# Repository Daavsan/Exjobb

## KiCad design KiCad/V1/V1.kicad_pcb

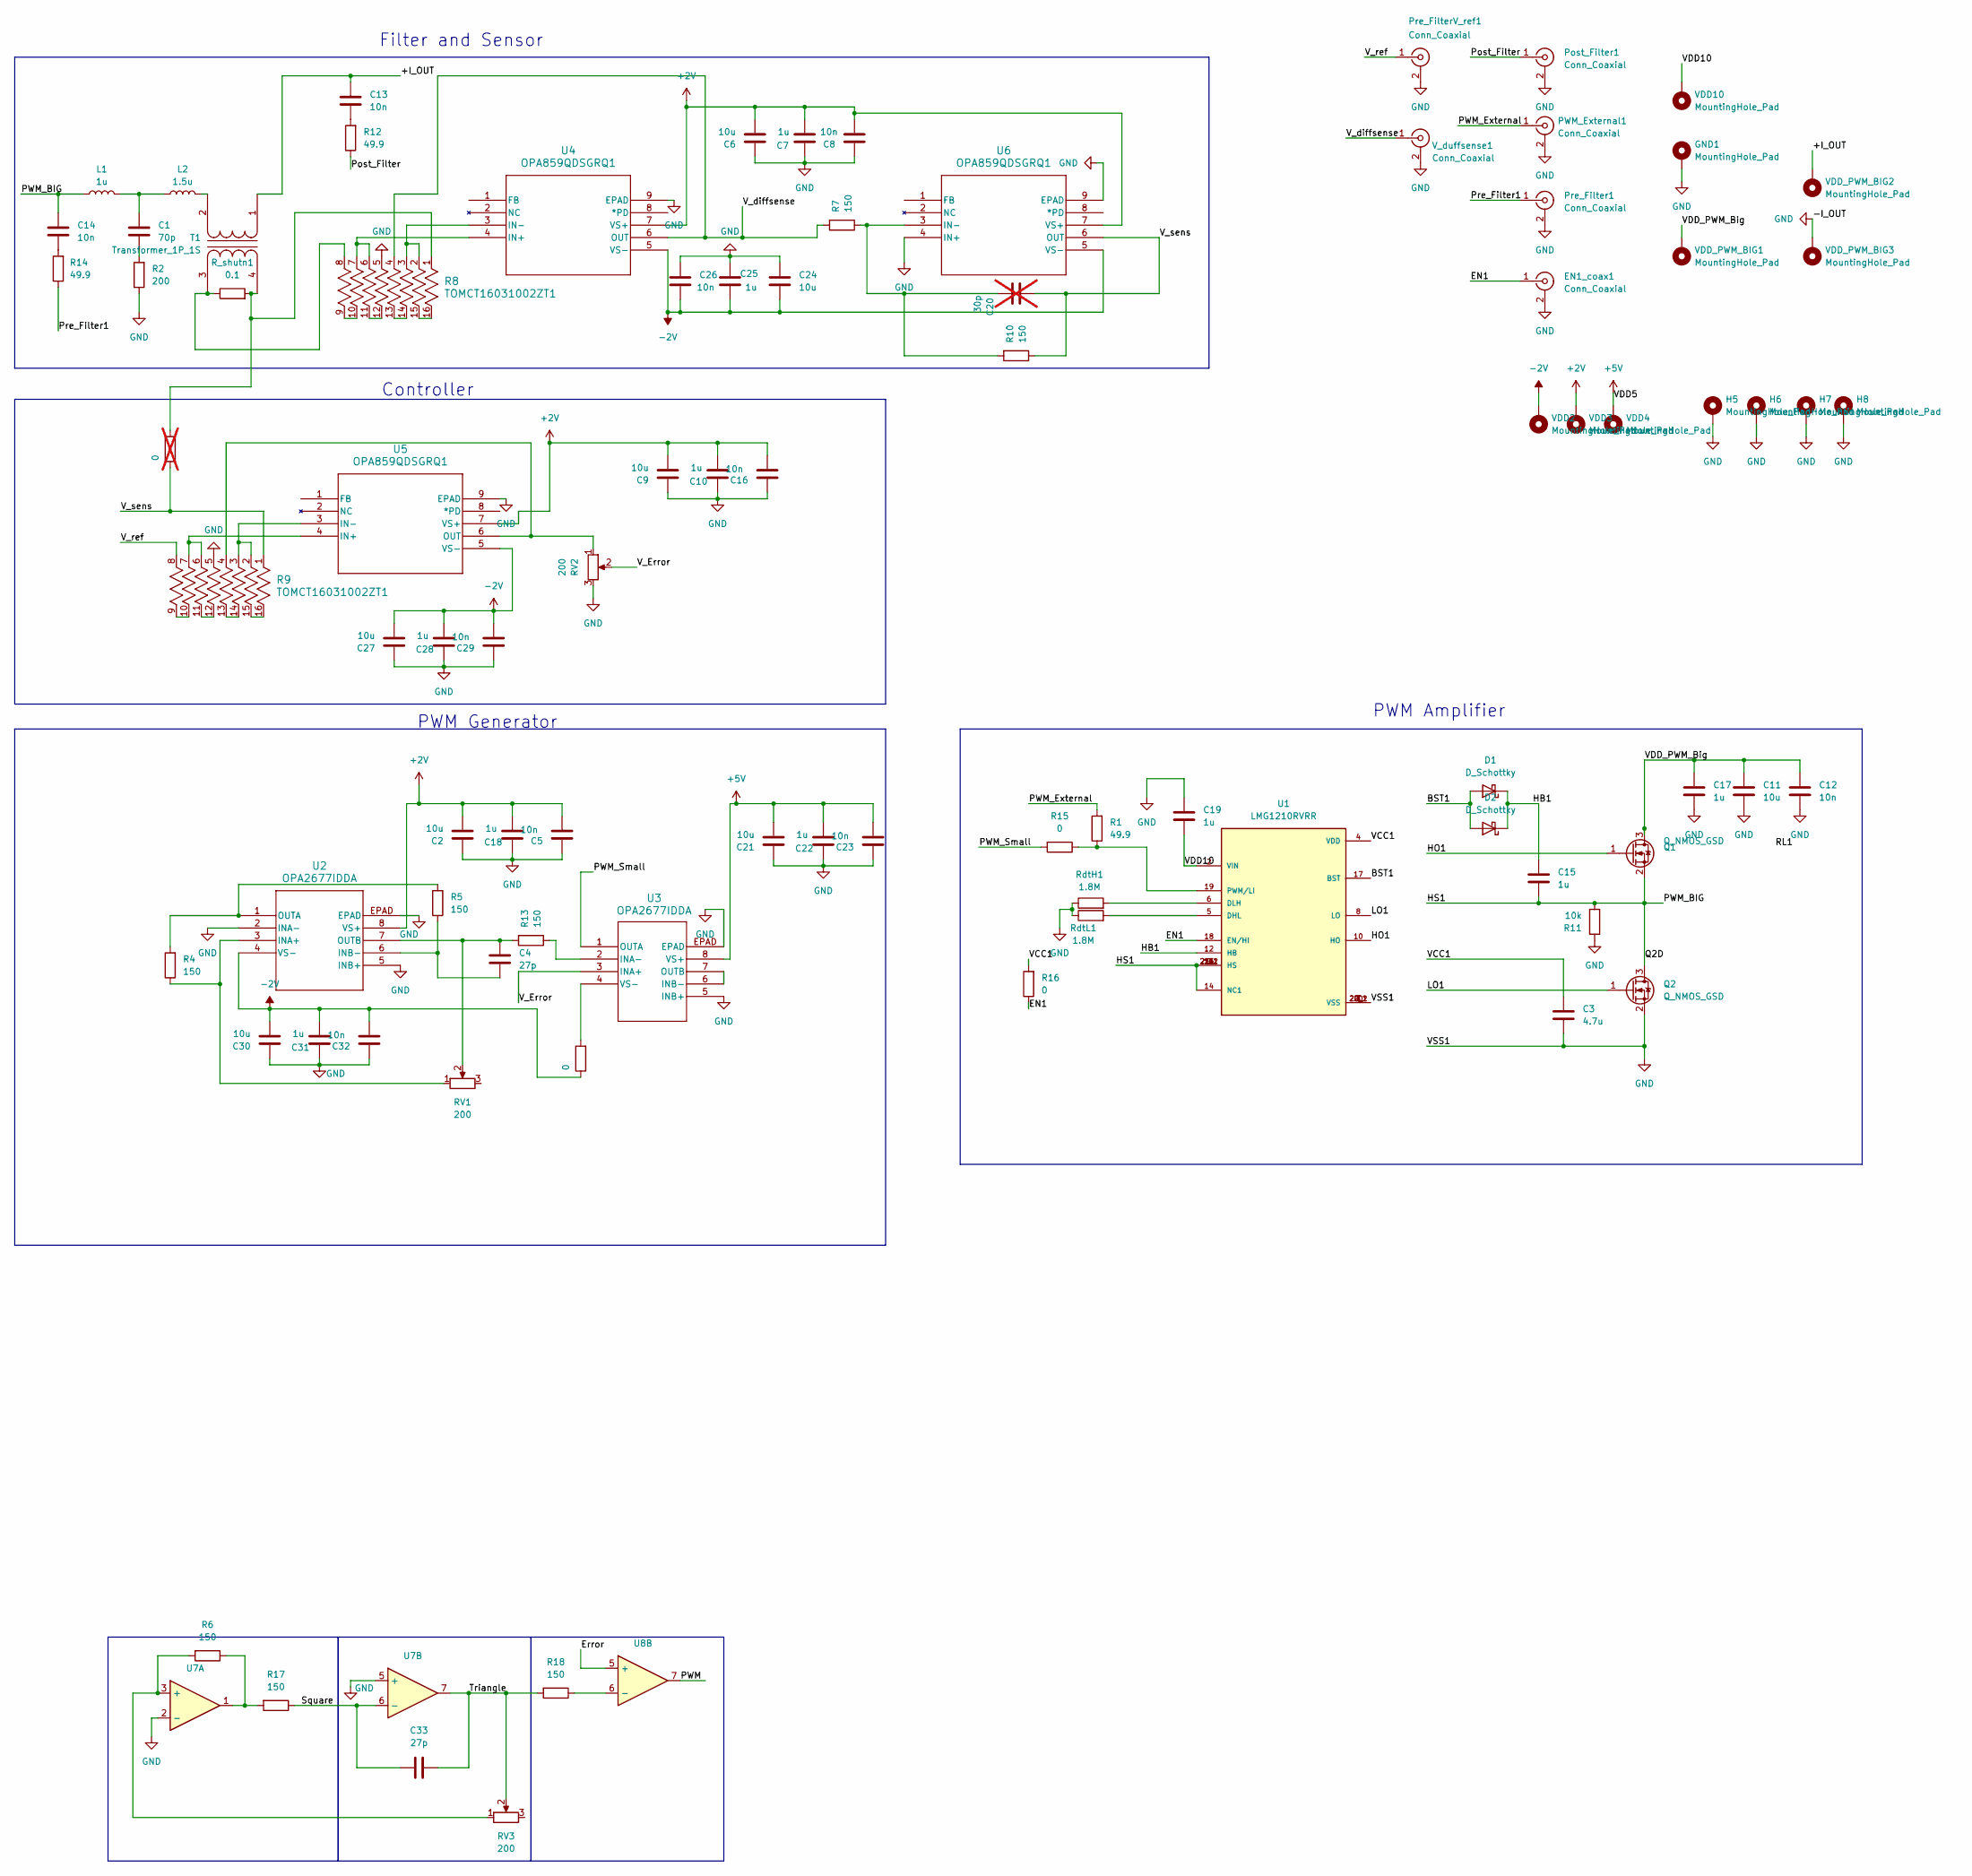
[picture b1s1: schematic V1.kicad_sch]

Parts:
C1: 70p; R_1206_3216Metric
C2, C21, C30: 10u; C_0402_1005Metric
C3: 4.7u; C_0603_1608Metric
C4, C33: 27p; C_0402_1005Metric
C5, C8, C13, C14, C16, C23, C26, C29, C32: 10n; C_0402_1005Metric
C6, C9, C24, C27: 10u; C_0603_1608Metric
C7, C10, C15, C18, C19, C22, C25, C28, C31: 1u; C_0402_1005Metric
C11: 10u; C_2220_5750Metric
C12: 10n; C_0805_2012Metric
C17: 1u; C_0805_2012Metric
C20: 30p; C_0402_1005Metric; not fitted
D1, D2: D_Schottky; SOT-323_SC-70
EN1_coax1: Conn_Coaxial; U.FL_Molex_MCRF_73412-0110_Vertical
GND1: MountingHole_Pad; MountingHole_2.5mm_Pad_TopBottom
H5, H6, H7, H8: MountingHole_Pad; MountingHole_4.3mm_M4_DIN965_Pad_TopBottom
L1: 1u; INductor_744060421
L2: 1.5u; INductor_744060421
PWM_External1: Conn_Coaxial; U.FL_Molex_MCRF_73412-0110_Vertical
Post_Filter1: Conn_Coaxial; U.FL_Molex_MCRF_73412-0110_Vertical
Pre_Filter1: Conn_Coaxial; U.FL_Molex_MCRF_73412-0110_Vertical
Pre_FilterV_ref1: Conn_Coaxial; U.FL_Molex_MCRF_73412-0110_Vertical
Q1, Q2: Q_NMOS_GSD; EPC8009
R1, R12, R14: 49.9; R_0402_1005Metric
R2: 200; R_1206_3216Metric
R3, R15, R16: 0; C_0805_2012Metric
R4, R5, R7, R10, R13: 150; R_0402_1005Metric
R6, R17, R18: 150
R8, R9: TOMCT16031002ZT1; NOMCT16031
R11: 10k; R_0402_1005Metric
R19: 0; C_0805_2012Metric; not fitted
RV1, RV2, RV3: 200; POT_ 3214W-1-201E
R_shutn1: 0.1; R_1020_2550Metric_Pad1.33x5.20mm_HandSolder
RdtH1: 1.8M; R_0402_1005Metric
RdtL1: 1.8M; R_0402_1005Metric
T1: Transformer_1P_1S; MyTransformer
U1: LMG1210RVRR; IC_LMG1210RVRR; PARTREV D
U2, U3: OPA2677IDDA; DDA8_3X2P49
U4, U5, U6: OPA859QDSGRQ1
U7: OPAMP
U8: Compariotr
VDD2, VDD3, VDD4, VDD10: MountingHole_Pad; TestPoint_THTPad_D2.5mm_Drill1.2mm
VDD_PWM_BIG1, VDD_PWM_BIG2, VDD_PWM_BIG3: MountingHole_Pad; MountingHole_2.5mm_Pad_TopBottom
V_duffsense1: Conn_Coaxial; U.FL_Molex_MCRF_73412-0110_Vertical

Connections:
+2V: C2.2, C5.2, C6.2, C7.2, C8.2, C9.2, C10.2, C16.2, C18.2, U2.8 (VS+), U4.7 (VS+), U5.7 (VS+), U6.7 (VS+), VDD3.1
+5V: C21.2, C22.2, C23.2, U3.8 (VS+), VDD4.1
-2V: C24.2, C25.2, C26.2, C27.2, C28.2, C29.2, C30.2, C31.2, C32.2, R3.1, U2.4 (VS-), U4.5 (VS-), U5.5 (VS-), U6.5 (VS-), VDD2.1
/+I_OUT: C13.2, T1.1 (AA), VDD_PWM_BIG2.1
/BST1: D1.1 (A), D2.1 (A), U1.17 (BST)
/EN1: EN1_coax1.1 (In), R16.1, U1.18 (EN/HI)
/HB1: C15.1, D1.3 (K), D2.3 (K), U1.12 (HB)
/HO1: Q1.1 (G), U1.10 (HO)
/HS1: C14.2, C15.2, L1.1, Q1.2 (S), Q2.3 (D), R11.1, U1.9 (HS), U1.13 (HS), U1.14 (NC1), U1.16 (HS), U1.21 (HS), U1.21_1 (HS), U1.21_2 (HS)
/LO1: Q2.1 (G), U1.8 (LO)
/PWM_External: PWM_External1.1 (In), R1.2
/PWM_Small: R15.2, U3.1 (OUTA)
/Post_Filter: Post_Filter1.1 (In), R12.1
/Pre_Filter1: Pre_Filter1.1 (In), R14.1
/VCC1: C3.1, R16.2, U1.4 (VDD)
/VDD10: C19.2, U1.2 (VIN), VDD10.1
/VDD_PWM_Big: C11.1, C12.1, C17.1, Q1.3 (D), VDD_PWM_BIG1.1
/V_Error: RV2.2, U3.3 (INA+)
/V_diffsense: R7.2, R8.4, U4.6 (OUT), V_duffsense1.1 (In)
/V_ref: Pre_FilterV_ref1.1 (In), R9.8
/V_sens: C20.1, R9.1, R10.1, R19.1, U6.6 (OUT)
GND: C2.1, C3.2, C5.1, C6.1, C7.1, C8.1, C9.1, C10.1, C11.2, C12.2, C16.1, C17.2, C18.1, C19.1, C21.1, C22.1, C23.1, C24.1, C25.1, C26.1, C27.1, C28.1, C29.1, C30.1, C31.1, C32.1, EN1_coax1.2 (Ext), GND1.1, H5.1, H6.1, H7.1, H8.1, PWM_External1.2 (Ext), Post_Filter1.2 (Ext), Pre_Filter1.2 (Ext), Pre_FilterV_ref1.2 (Ext), Q2.2 (S), R2.1, R8.5, R9.5, R11.2, RV2.3, RdtH1.1, RdtL1.1, U1.3 (VSS), U1.7 (VSS), U1.20 (VSS), U1.20_1 (VSS), U1.20_2 (VSS), U2.2 (INA-), U2.5 (INB+), U2.EPAD, U3.5 (INB+), U3.EPAD, U4.9 (EPAD), U5.9 (EPAD), U6.4 (IN+), U6.9 (EPAD), U7.2 (-), U7.5 (+), VDD_PWM_BIG3.1, V_duffsense1.2 (Ext)
unnamed: C1.1, L1.2, L2.1
unnamed: C1.2, R2.2
unnamed: C13.1, R12.2
unnamed: C14.1, R14.2
unnamed: C33.1, R17.1, U7.6 (-)
unnamed: C33.2, R18.2, RV3.2, U7.7
unnamed: R6.2, RV3.1, U7.3 (+)
unnamed: R8.9, R8.10
unnamed: R8.11, R8.12
unnamed: R8.13, R8.14
unnamed: R8.15, R8.16
unnamed: R9.9, R9.10
unnamed: R9.11, R9.12
unnamed: R9.13, R9.14
unnamed: R9.15, R9.16
unnamed: R6.1, R17.2, U7.1
unnamed: R18.1, U8.6 (-)
unnamed: L2.2, T1.2 (AB)
unnamed: R8.8, R_shutn1.1, T1.3 (SA)
unnamed: R8.1, R19.2, R_shutn1.2, T1.4 (SB)
unnamed: RdtL1.2, U1.5 (DHL)
unnamed: RdtH1.2, U1.6 (DLH)
unnamed: R1.1, R15.1, U1.19 (PWM/LI)
unnamed: R4.1, RV1.1, U2.3 (INA+)
unnamed: C4.1, R5.1, U2.6 (INB-)
unnamed: R4.2, R5.2, U2.1 (OUTA)
unnamed: C4.2, R13.2, RV1.2, U2.7 (OUTB)
unnamed: R13.1, U3.2 (INA-)
unnamed: U3.6 (INB-), U3.7 (OUTB)
unnamed: R3.2, U3.4 (VS-)
unnamed: R8.6, R8.7, U4.4 (IN+)
unnamed: R8.2, R8.3, U4.3 (IN-)
unnamed: R9.6, R9.7, U5.4 (IN+)
unnamed: R9.2, R9.3, U5.3 (IN-)
unnamed: R9.4, RV2.1, U5.6 (OUT)
unnamed: C20.2, R7.1, R10.2, U6.3 (IN-)

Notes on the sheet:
Controller
Filter and Sensor
PWM Generator
PWM Amplifier

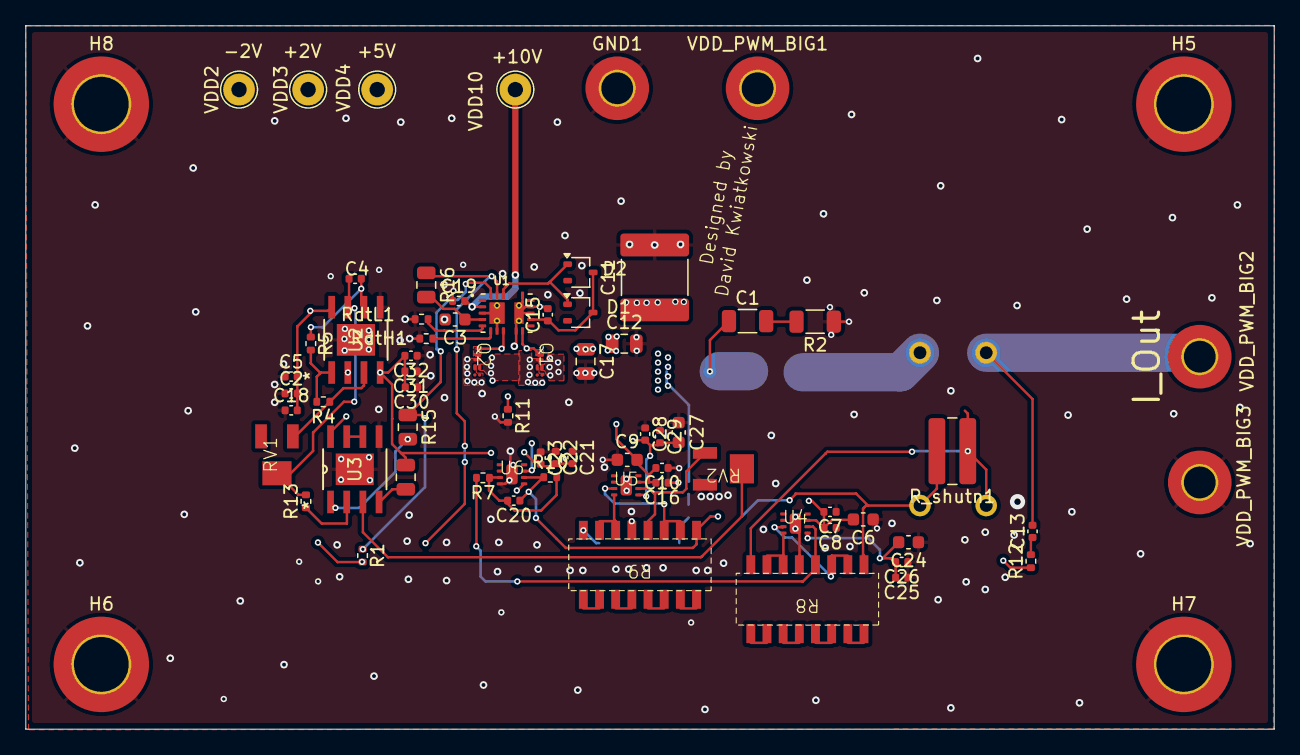
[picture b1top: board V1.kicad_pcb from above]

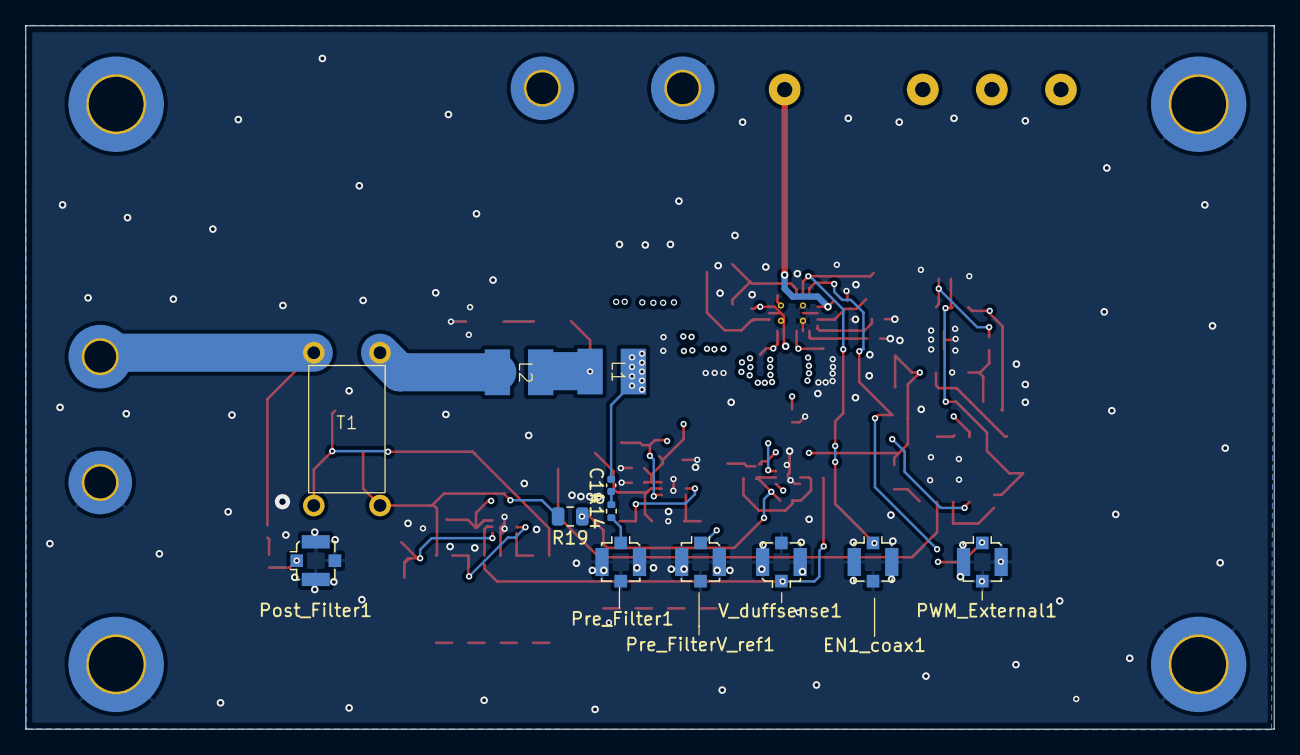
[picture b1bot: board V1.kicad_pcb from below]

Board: 4 copper layers, 98.0 x 55.2 mm, 84 parts (12 on the bottom side), 53 nets.

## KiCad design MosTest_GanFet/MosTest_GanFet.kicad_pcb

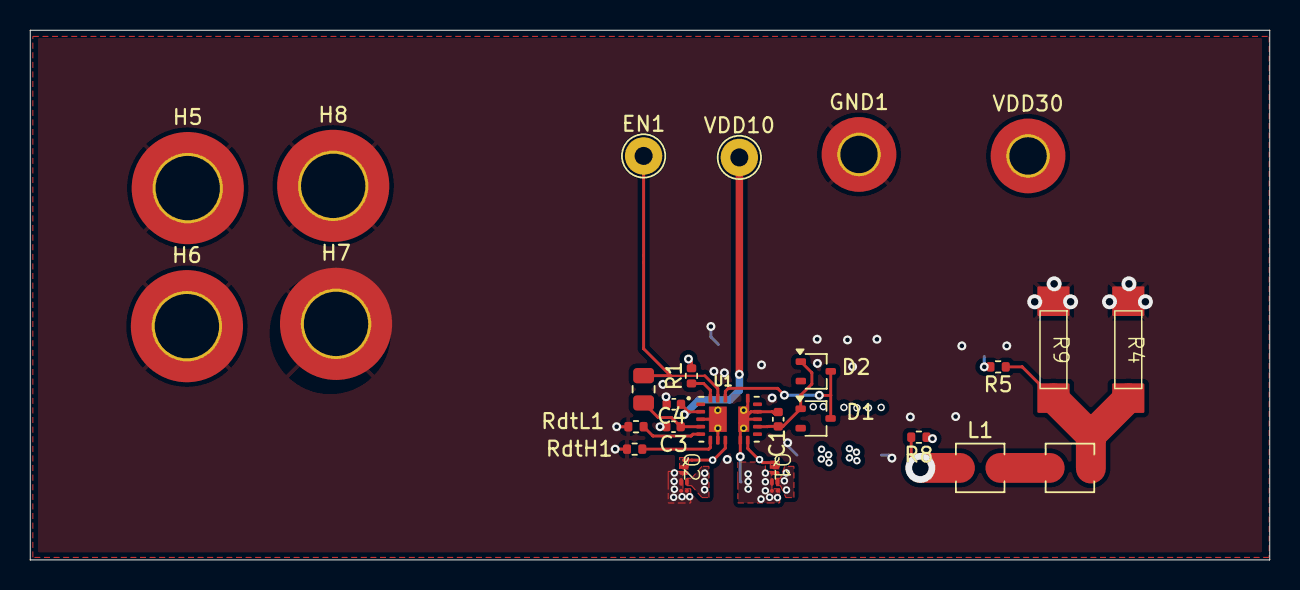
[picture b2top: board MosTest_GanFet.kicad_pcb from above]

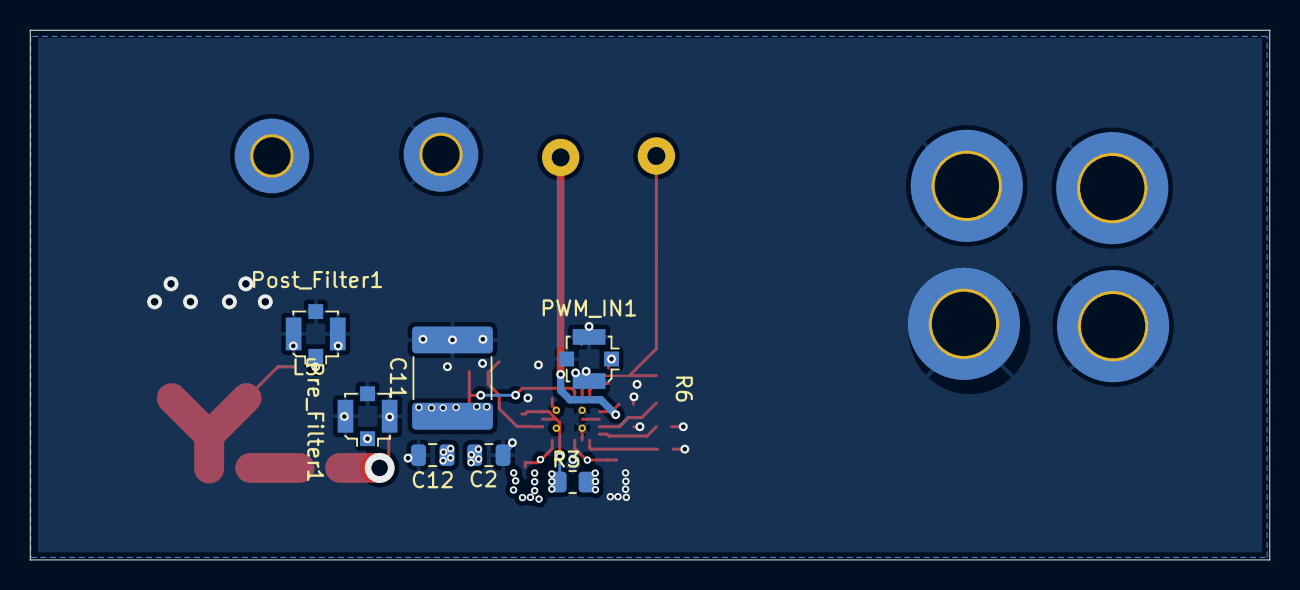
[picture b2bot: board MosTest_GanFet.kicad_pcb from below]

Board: 4 copper layers, 82.9 x 35.4 mm, 33 parts (7 on the bottom side), 19 nets.

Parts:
C1, C4: 1u; C_0402_1005Metric
C2: 1u; C_0805_2012Metric
C3: 4.7u; C_0402_1005Metric
C11: 22u; C_2220_5750Metric
C12: 10n; C_0805_2012Metric
D1, D2: D_Schottky; SOT-323_SC-70
EN1: MountingHole_Pad; TestPoint_THTPad_D2.5mm_Drill1.2mm
GND1: MountingHole_Pad; MountingHole_2.5mm_Pad_TopBottom
H5, H6, H7, H8: MountingHole_Pad; MountingHole_4.3mm_M4_DIN965_Pad_TopBottom
L1, L5: L; L_Vishay_IHLP-1212
PWM_IN1: Conn_Coaxial; U.FL_Molex_MCRF_73412-0110_Vertical
Post_Filter1: Conn_Coaxial; U.FL_Molex_MCRF_73412-0110_Vertical
Pre_Filter1: Conn_Coaxial; U.FL_Molex_MCRF_73412-0110_Vertical
Q1, Q2: Q_NMOS_GSD; EPC8009
R1, R5, R8: 47; R_0402_1005Metric
R3, R6: 0; R_0805_2012Metric
R4, R9: 470; RWS5
RdtH1: 1.8M; R_0402_1005Metric
RdtL1: 1.8M; R_0402_1005Metric
U1: LMG1210RVRR; IC_LMG1210RVRR
VDD10: MountingHole_Pad; TestPoint_THTPad_D2.5mm_Drill1.2mm
VDD30: MountingHole_Pad; MountingHole_2.5mm_Pad_TopBottom

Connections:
/BST1: D1.3 (A), D2.3 (A), U1.17 (BST)
/EN1: EN1.1, R6.1, U1.18 (EN/HI)
/HB1: C1.1, D1.1 (K), D2.1 (K), U1.12 (HB)
/HO1: Q1.1 (G), U1.10 (HO)
/HS1: C1.2, L1.1, Q1.2 (S), Q1.3 (D), Q1.5, Q1.6, R3.2, R8.2, U1.9 (HS), U1.13 (HS), U1.14 (NC1), U1.16 (HS), U1.21 (HS), U1.21_1 (HS), U1.21_2 (HS)
/LO1: Q2.1 (G), U1.8 (LO)
/N1RL: L5.2, R4.2, R5.1, R9.2
/PWM1: PWM_IN1.1 (In), R1.2
/Pre_Filter1: Pre_Filter1.1 (In), R8.1
/Q2D: Q2.4, R3.1
/RL1: Post_Filter1.1 (In), R5.2
/VCC1: C3.1, R6.2, U1.4 (VDD)
/VDD10: C4.2, U1.2 (VIN), VDD10.1
/VDD30: C2.1, C11.1, C12.1, Q1.4, VDD30.1
GND: C2.2, C3.2, C4.1, C11.2, C12.2, GND1.1, H5.1, H6.1, H7.1, H8.1, PWM_IN1.2 (Ext), Post_Filter1.2 (Ext), Pre_Filter1.2 (Ext), Q2.2 (S), Q2.3 (D), Q2.5, Q2.6, R4.1, R9.1, RdtH1.1, RdtL1.1, U1.3 (VSS), U1.7 (VSS), U1.20 (VSS), U1.20_1 (VSS), U1.20_2 (VSS)
unnamed: L1.2, L5.1
unnamed: RdtL1.2, U1.5 (DHL)
unnamed: RdtH1.2, U1.6 (DLH)
unnamed: R1.1, U1.19 (PWM/LI)

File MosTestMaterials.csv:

"Reference","Value","Datasheet","Footprint","Qty","DNP"
"C1,C2,C4","1u","~","-- mixed values --","3",""
"C3","4.7u","~","Capacitor_SMD:C_0402_1005Metric","1",""
"C11","22u","~","Capacitor_SMD:C_2220_5750Metric","1",""
"C12","10n","~","Capacitor_SMD:C_0805_2012Metric","1",""
"D1,D2","D_Schottky","~","Package_TO_SOT_SMD:SOT-323_SC-70","2",""
"L1,L5","L","~","Inductor_SMD:L_Vishay_IHLP-1212","2",""
"Post_Filter1,Pre_Filter1,PWM_IN1","Conn_Coaxial","~","Connector_Coaxial:U.FL_Molex_MCRF_73412-0110_Vertical","3",""
"Q1,Q2","Q_NMOS_GSD","~","Package_TO_SOT_THT:TO-220-3_Vertical","2",""
"R1,R5,R8","47","~","Resistor_SMD:R_0402_1005Metric","3",""
"R3,R6","0","~","Resistor_SMD:R_0805_2012Metric","2",""
"R4,R9","470","~","MyResistors:RWS5","2",""
"RdtH1,RdtL1","1.8M","~","Resistor_SMD:R_0402_1005Metric","2",""
"U1","LMG1210RVRR","","Drivers:IC_LMG1210RVRR","1",""

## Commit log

2024-10-29 added stuff
2024-10-29 add laptop stuff
2024-10-29 added more tests
2024-10-29 matlap osscilisope plot function
2024-11-01 more stuff idk
2024-11-01 switch loss matlab script bugfix
2024-11-05 plotter and more files
2024-11-05 pictures folder (billder)
2024-11-05 more mesurments and added plotter rescale function
2024-11-14 filters
2024-11-14 filters wokring :]
2024-11-15 kickad start and simulation changes
2024-11-17 kicad scematic
2024-11-19 asdaslkwrjhsoid7ty
2024-11-21 Worked on V1 PCB
2024-11-22 added integrator
2024-11-22 eddit
2024-11-25 V1 pcb almost done
2024-11-25 V1 done
2024-11-25 Fixed GanfetPad clerance
2024-11-27 Borgs pcb via addition
2024-11-27 Fixed driver missing mask layer
2024-12-04 boom
2024-12-11 värmebilder
2024-12-11 pott pwm gen stuff
2024-12-11 added pwm out plot
2024-12-17 boom and stuff
2025-01-10 fixed pwm gen negative supply voltage
2025-01-10 aded alternative path for curent sense signal
2025-01-17 v1 mes
2025-01-27 ccdesign matlab
2025-02-02 state of the art
2025-02-14 jag vet inte
